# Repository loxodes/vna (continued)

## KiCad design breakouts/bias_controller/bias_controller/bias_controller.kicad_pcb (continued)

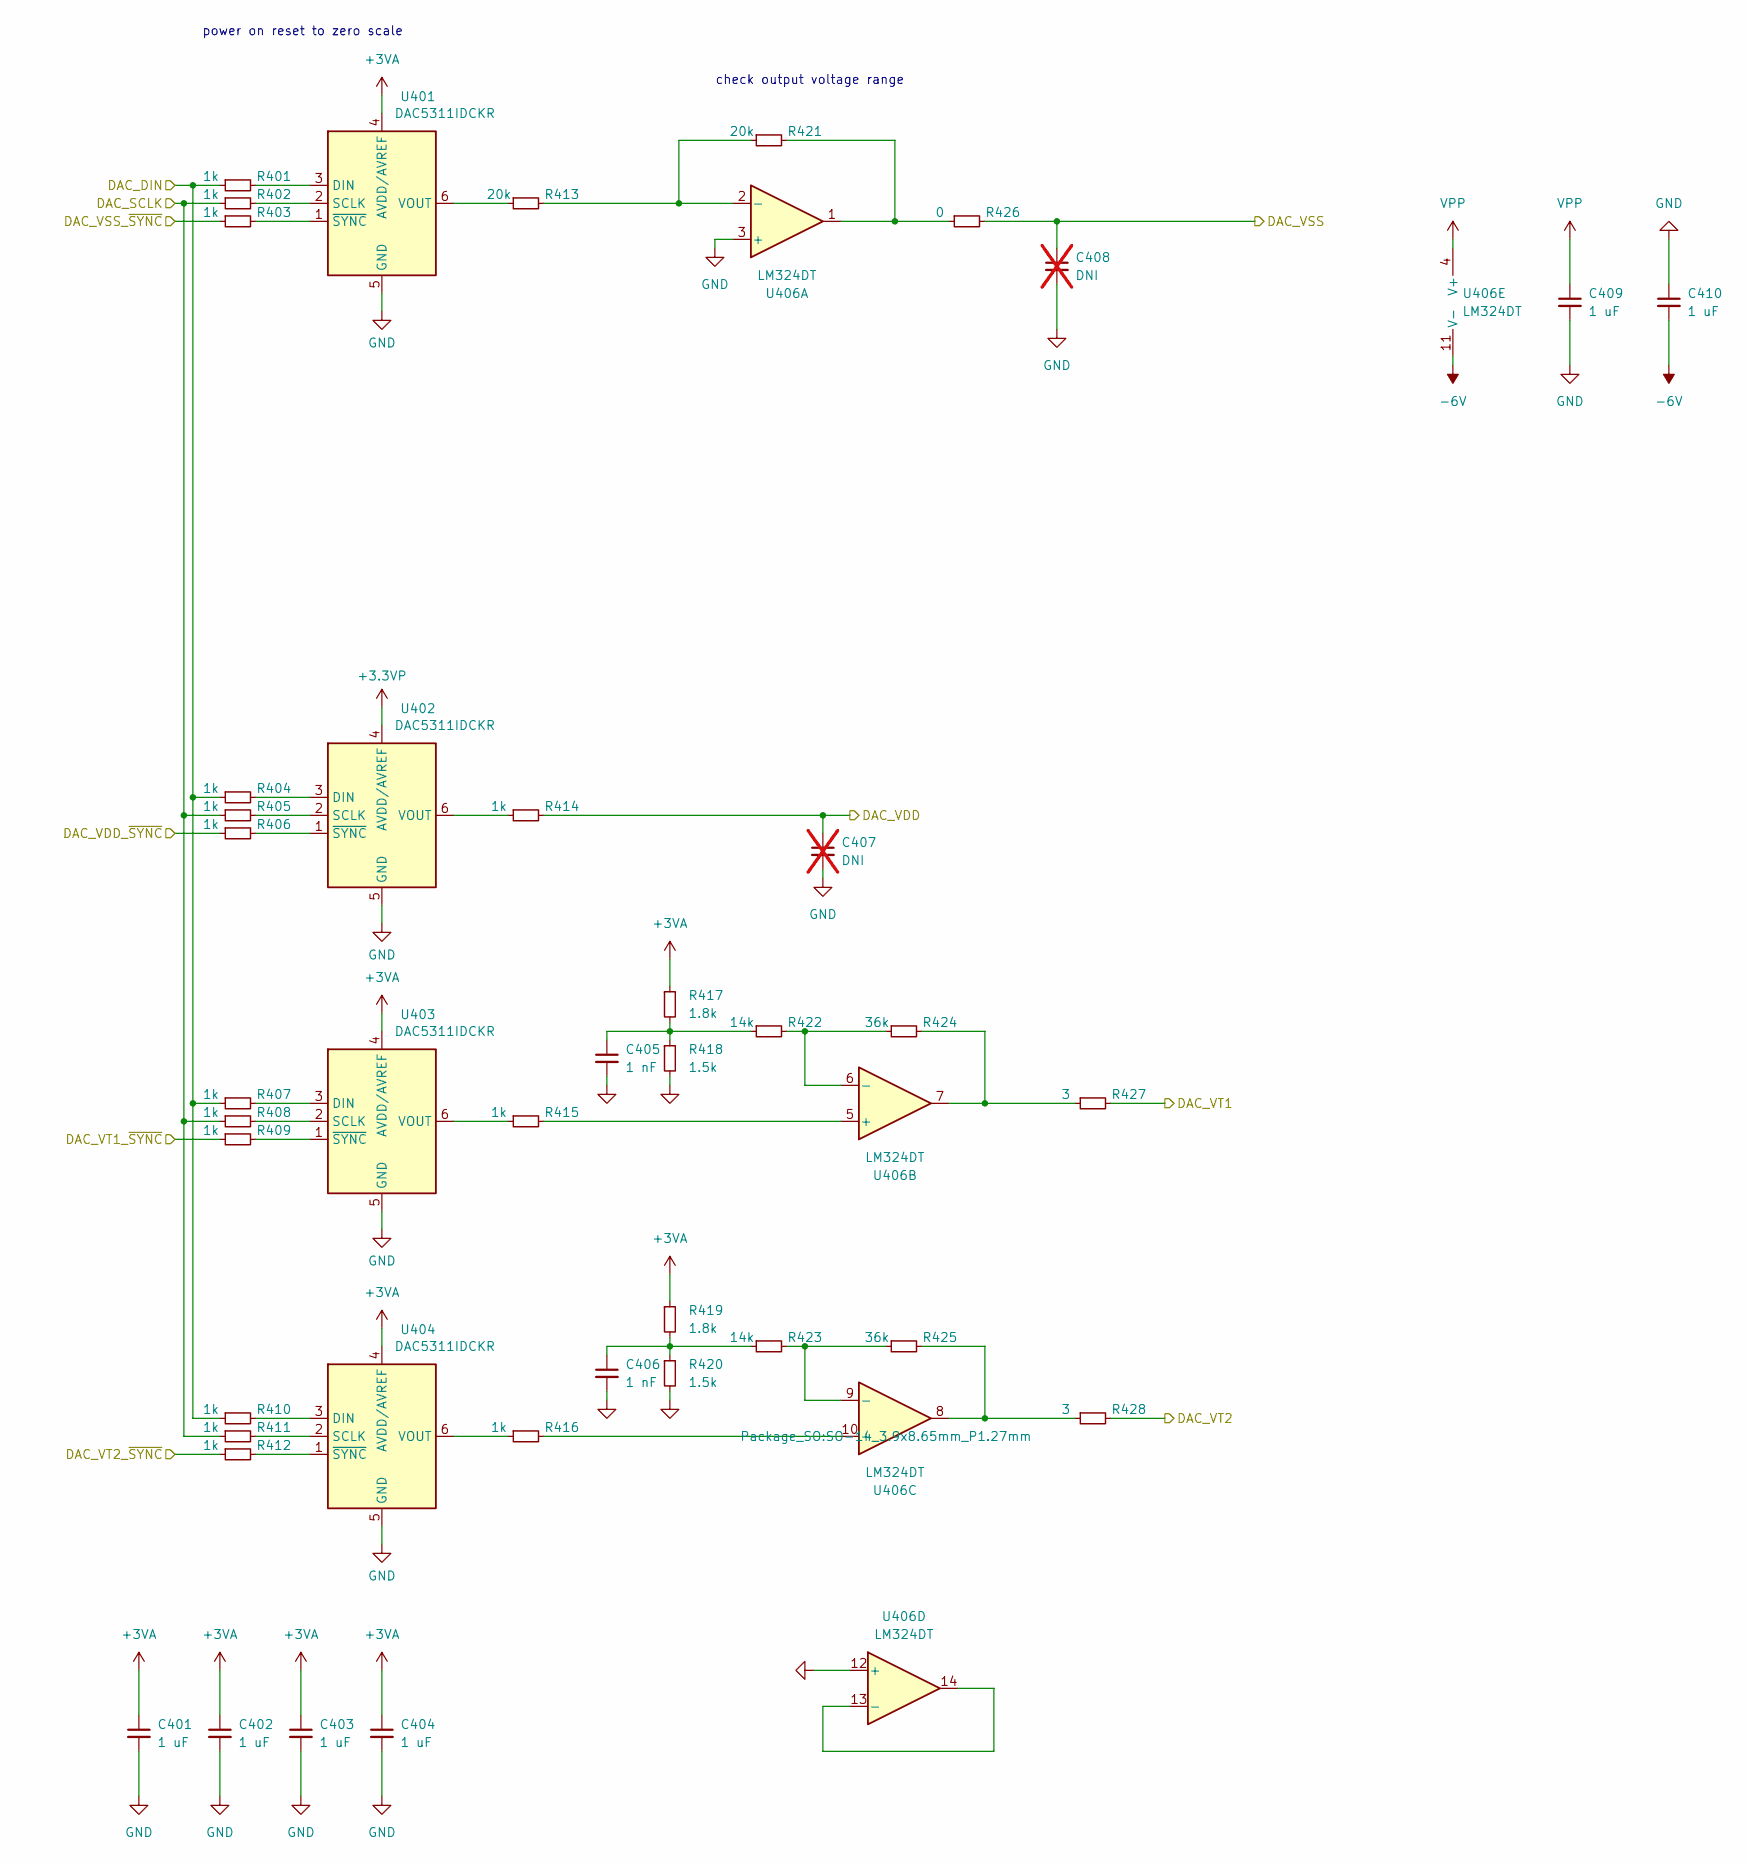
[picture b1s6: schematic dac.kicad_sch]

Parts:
C401, C402, C403, C404, C409, C410: 1 uF; C_0402_1005Metric
C405, C406: 1 nF; C_0402_1005Metric
C407, C408: DNI; C_0402_1005Metric; not fitted
R401, R402, R403, R404, R405, R406, R407, R408, R409, R410, R411, R412, R414, R415, R416: 1k; R_0402_1005Metric
R413, R421: 20k; R_0402_1005Metric
R417, R419: 1.8k; R_0402_1005Metric
R418, R420: 1.5k; R_0402_1005Metric
R422, R423: 14k; R_0402_1005Metric
R424, R425: 36k; R_0402_1005Metric
R426: 0; R_0402_1005Metric
R427, R428: 3; R_0402_1005Metric
U401, U402, U403, U404: DAC5311IDCKR; SOT-363_SC-70-6
U406: LM324DT; SO-14_3.9x8.65mm_P1.27mm

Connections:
+3.3VP: U402.4 (AVDD/AVREF); also elsewhere on the board
+3VA: C401.1, C402.1, C403.1, C404.1, R417.1, R419.1, U401.4 (AVDD/AVREF), U403.4 (AVDD/AVREF), U404.4 (AVDD/AVREF); also elsewhere on the board
-6V: C410.2, U406.11 (V-); also elsewhere on the board
/dac/DAC_DIN: R401.1, R404.1, R407.1, R410.1; also elsewhere on the board
/dac/DAC_SCLK: R402.1, R405.1, R408.1, R411.1; also elsewhere on the board
/dac/DAC_VDD: C407.1, R414.2; also elsewhere on the board
/dac/DAC_VDD_~SYNC: R406.1; also elsewhere on the board
/dac/DAC_VSS: C408.1, R426.2; also elsewhere on the board
/dac/DAC_VSS_~SYNC: R403.1; also elsewhere on the board
/dac/DAC_VT1: R427.2; also elsewhere on the board
/dac/DAC_VT1_~SYNC: R409.1; also elsewhere on the board
/dac/DAC_VT2: R428.2; also elsewhere on the board
/dac/DAC_VT2_~SYNC: R412.1; also elsewhere on the board
GND: C401.2, C402.2, C403.2, C404.2, C405.2, C406.2, C407.2, C408.2, C409.2, C410.1, R418.2, R420.2, U401.5 (GND), U402.5 (GND), U403.5 (GND), U404.5 (GND), U406.3 (+), U406.12 (+); also elsewhere on the board
unnamed: C405.1, R417.2, R418.1, R422.1
unnamed: C406.1, R419.2, R420.1, R423.1
unnamed: R421.2, R426.1, U406.1
unnamed: R424.2, R427.1, U406.7
unnamed: R425.2, R428.1, U406.8
unnamed: R401.2, U401.3 (DIN)
unnamed: R402.2, U401.2 (SCLK)
unnamed: R413.1, U401.6 (VOUT)
unnamed: R403.2, U401.1 (~SYNC)
unnamed: R404.2, U402.3 (DIN)
unnamed: R405.2, U402.2 (SCLK)
unnamed: R414.1, U402.6 (VOUT)
unnamed: R406.2, U402.1 (~SYNC)
unnamed: R407.2, U403.3 (DIN)
unnamed: R408.2, U403.2 (SCLK)
unnamed: R415.1, U403.6 (VOUT)
unnamed: R409.2, U403.1 (~SYNC)
unnamed: R410.2, U404.3 (DIN)
unnamed: R411.2, U404.2 (SCLK)
unnamed: R416.1, U404.6 (VOUT)
unnamed: R412.2, U404.1 (~SYNC)
unnamed: R413.2, R421.1, U406.2 (-)
unnamed: R415.2, U406.5 (+)
unnamed: R422.2, R424.1, U406.6 (-)
unnamed: R416.2, U406.10 (+)
unnamed: R423.2, R425.1, U406.9 (-)
unnamed: U406.13 (-), U406.14
VPP: C409.1, U406.4 (V+); also elsewhere on the board

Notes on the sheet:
check output voltage range
power on reset to zero scale

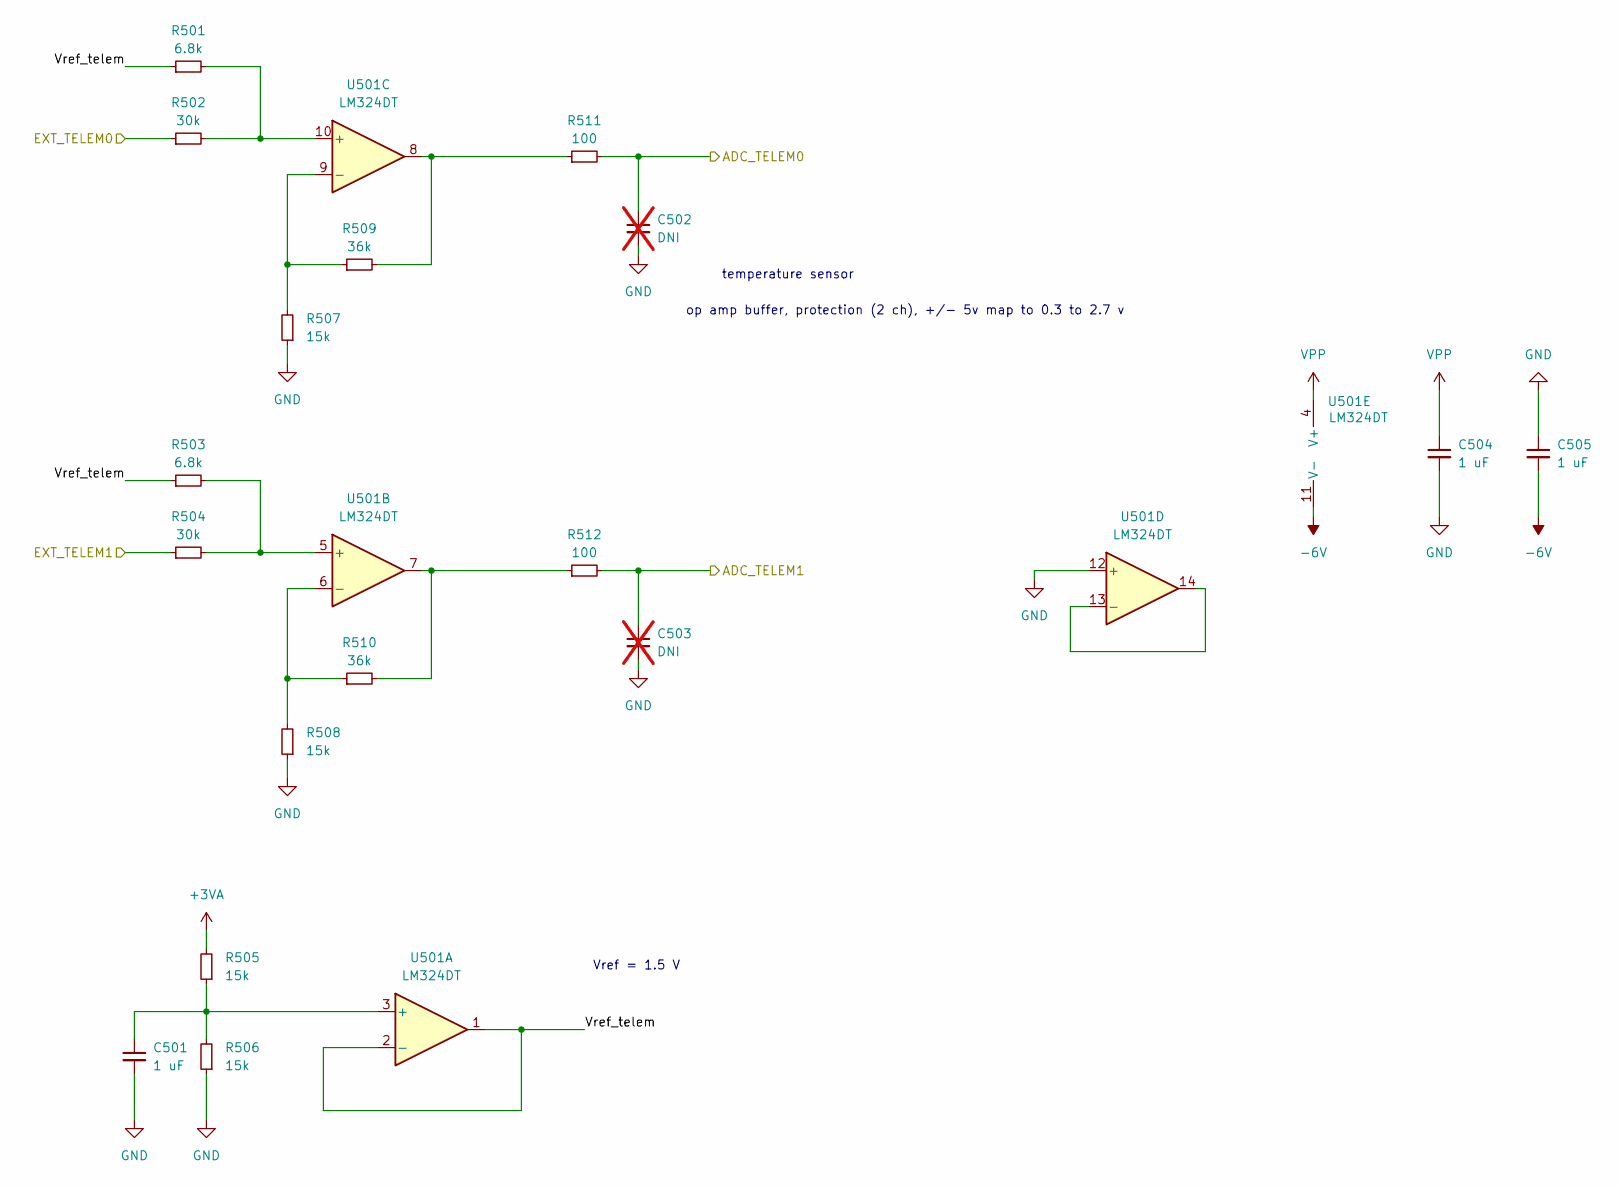
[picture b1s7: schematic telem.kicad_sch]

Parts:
C501, C504, C505: 1 uF; C_0402_1005Metric
C502, C503: DNI; C_0402_1005Metric; not fitted
R501, R503: 6.8k; R_0402_1005Metric
R502, R504: 30k; R_0402_1005Metric
R505, R506, R507, R508: 15k; R_0402_1005Metric
R509, R510: 36k; R_0402_1005Metric
R511, R512: 100; R_0402_1005Metric
U501: LM324DT; SO-14_3.9x8.65mm_P1.27mm

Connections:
+3VA: R505.2; also elsewhere on the board
-6V: C505.2, U501.11 (V-); also elsewhere on the board
/ext_conn/EXT_TELEM0: R502.1; also elsewhere on the board
/ext_conn/EXT_TELEM1: R504.1; also elsewhere on the board
/mcu/ADC_TELEM0: C502.1, R511.2; also elsewhere on the board
/mcu/ADC_TELEM1: C503.1, R512.2; also elsewhere on the board
/telemetry/Vref_telem: R501.1, R503.1, U501.1, U501.2 (-)
GND: C501.2, C502.2, C503.2, C504.2, C505.1, R506.1, R507.1, R508.1, U501.12 (+); also elsewhere on the board
unnamed: R509.2, R511.1, U501.8
unnamed: R510.2, R512.1, U501.7
unnamed: C501.1, R505.1, R506.2, U501.3 (+)
unnamed: R503.2, R504.2, U501.5 (+)
unnamed: R508.2, R510.1, U501.6 (-)
unnamed: R501.2, R502.2, U501.10 (+)
unnamed: R507.2, R509.1, U501.9 (-)
unnamed: U501.13 (-), U501.14
VPP: C504.1, U501.4 (V+); also elsewhere on the board

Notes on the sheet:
op amp buffer, protection (2 ch), +/- 5v map to 0.3 to 2.7 v
temperature sensor
Vref = 1.5 V

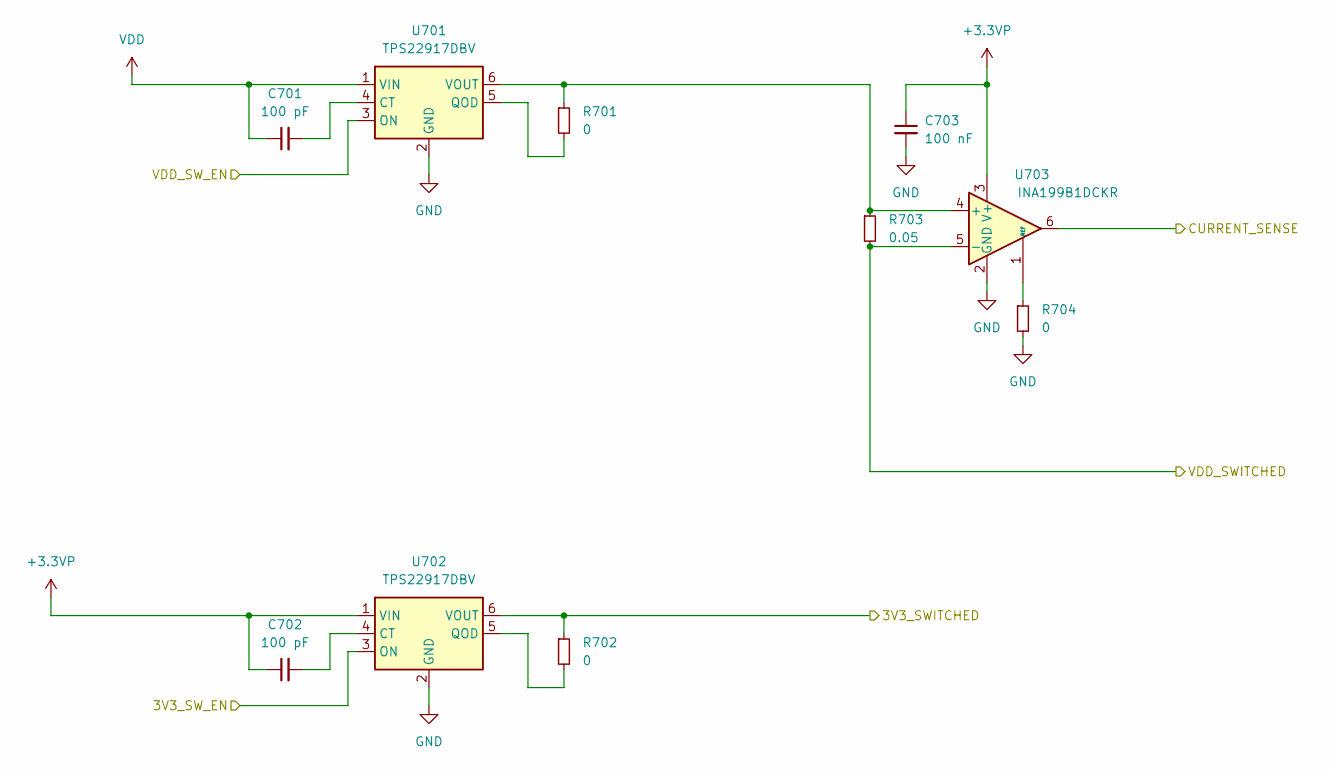
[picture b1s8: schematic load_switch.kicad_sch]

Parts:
C701, C702: 100 pF; C_0402_1005Metric
C703: 100 nF; C_0402_1005Metric
R701, R702: 0; R_0402_1005Metric
R703: 0.05; R_1206_3216Metric
R704: 0; R_1206_3216Metric
U701, U702: TPS22917DBV; SOT-23-6
U703: INA199B1DCKR; SOT-363_SC-70-6

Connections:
+3.3VP: C702.1, C703.1, U702.1 (VIN), U703.3 (V+); also elsewhere on the board
/ext_conn/3V3_SWITCHED: R702.1, U702.6 (VOUT); also elsewhere on the board
/ext_conn/VDD_SWITCHED: R703.2, U703.5 (-); also elsewhere on the board
/load switch/CURRENT_SENSE: U703.6; also elsewhere on the board
/mcu/3V3_SW_EN: U702.3 (ON); also elsewhere on the board
/mcu/VDD_SW_EN: U701.3 (ON); also elsewhere on the board
GND: C703.2, R704.2, U701.2 (GND), U702.2 (GND), U703.2 (GND); also elsewhere on the board
unnamed: C701.2, U701.4 (CT)
unnamed: R701.2, U701.5 (QOD)
unnamed: R701.1, R703.1, U701.6 (VOUT), U703.4 (+)
unnamed: C702.2, U702.4 (CT)
unnamed: R702.2, U702.5 (QOD)
unnamed: R704.1, U703.1 (REF)
VDD: C701.1, U701.1 (VIN); also elsewhere on the board

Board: 2 copper layers, 203 parts (0 on the bottom side), 164 nets, no tracks yet.

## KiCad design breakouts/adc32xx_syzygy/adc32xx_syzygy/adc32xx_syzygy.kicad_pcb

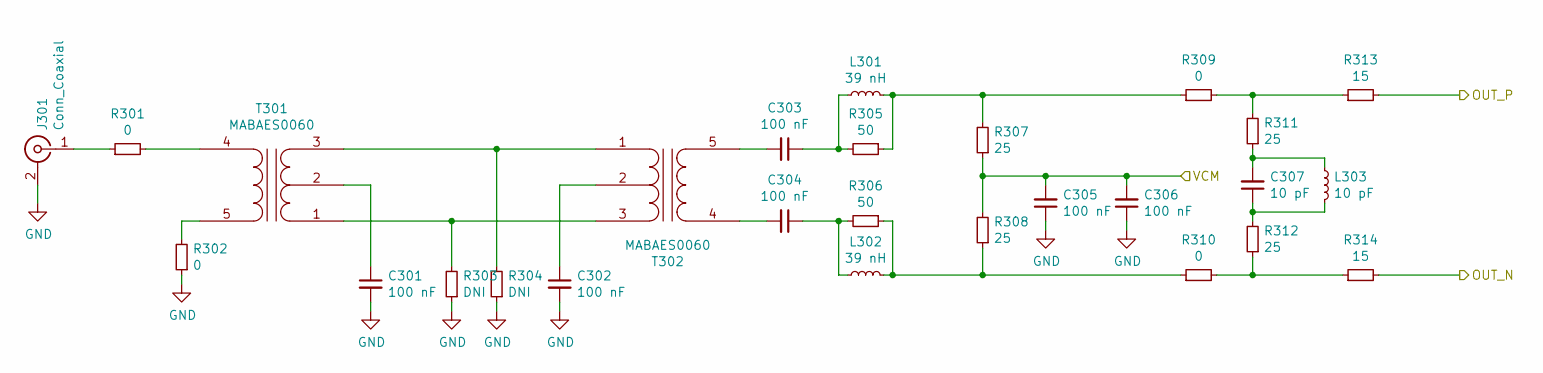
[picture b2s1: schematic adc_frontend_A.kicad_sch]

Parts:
C301, C302, C303, C304, C305, C306: 100 nF; C_0402_1005Metric
C307: 10 pF; C_0402_1005Metric
J301: Conn_Coaxial; SMA_Cinch_142-0711-821_EdgeMount
L301, L302: 39 nH; R_0402_1005Metric
L303: 10 pF; R_0402_1005Metric
R301, R302, R309, R310: 0; R_0402_1005Metric
R303, R304: DNI; R_0402_1005Metric
R305, R306: 50; R_0402_1005Metric
R307, R308, R311, R312: 25; R_0402_1005Metric
R313, R314: 15; R_0402_1005Metric
T301, T302: MABAES0060; 5LEAD_BALUN_4p83mm_3p3mm

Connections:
/VCM: C305.2, C306.2, R307.1, R308.2; also elsewhere on the board
/adc/IN_A_N: R314.2; also elsewhere on the board
/adc/IN_A_P: R313.2; also elsewhere on the board
GND: C301.2, C302.2, C305.1, C306.1, J301.2 (Ext), R302.1, R303.1, R304.1; also elsewhere on the board
unnamed: C303.1, L301.1, R305.2
unnamed: C304.1, L302.1, R306.2
unnamed: C307.1, L303.2, R312.2
unnamed: C307.2, L303.1, R311.1
unnamed: J301.1 (In), R301.1
unnamed: L301.2, R305.1, R307.2, R309.1
unnamed: L302.2, R306.1, R308.1, R310.1
unnamed: R309.2, R311.2, R313.1
unnamed: R310.2, R312.1, R314.1
unnamed: C301.1, T301.2 (PM)
unnamed: R303.2, T301.1 (PR1), T302.3 (PR2)
unnamed: R304.2, T301.3 (PR2), T302.1 (PR1)
unnamed: R301.2, T301.4 (S1)
unnamed: R302.2, T301.5 (S2)
unnamed: C302.1, T302.2 (PM)
unnamed: C304.2, T302.4 (S1)
unnamed: C303.2, T302.5 (S2)

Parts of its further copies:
C401, C402, C403, C404, C405, C406: 100 nF; C_0402_1005Metric
C407: 10 pF; C_0402_1005Metric
J401: Conn_Coaxial; SMA_Cinch_142-0711-821_EdgeMount
L401, L402: 39 nH; R_0402_1005Metric
L403: 10 pF; R_0402_1005Metric
R401, R402, R409, R410: 0; R_0402_1005Metric
R403, R404: DNI; R_0402_1005Metric
R405, R406: 50; R_0402_1005Metric
R407, R408, R411, R412: 25; R_0402_1005Metric
R413, R414: 15; R_0402_1005Metric
T401, T402: MABAES0060; 5LEAD_BALUN_4p83mm_3p3mm

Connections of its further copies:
/VCM: C405.2, C406.2, R407.1, R408.2; also elsewhere on the board
/adc/IN_B_N: R414.2; also elsewhere on the board
/adc/IN_B_P: R413.2; also elsewhere on the board
GND: C401.2, C402.2, C405.1, C406.1, J401.2 (Ext), R402.1, R403.1, R404.1; also elsewhere on the board
unnamed: C403.1, L401.1, R405.2
unnamed: C404.1, L402.1, R406.2
unnamed: C407.1, L403.2, R412.2
unnamed: C407.2, L403.1, R411.1
unnamed: J401.1 (In), R401.1
unnamed: L401.2, R405.1, R407.2, R409.1
unnamed: L402.2, R406.1, R408.1, R410.1
unnamed: R409.2, R411.2, R413.1
unnamed: R410.2, R412.1, R414.1
unnamed: C401.1, T401.2 (PM)
unnamed: R403.2, T401.1 (PR1), T402.3 (PR2)
unnamed: R404.2, T401.3 (PR2), T402.1 (PR1)
unnamed: R401.2, T401.4 (S1)
unnamed: R402.2, T401.5 (S2)
unnamed: C402.1, T402.2 (PM)
unnamed: C404.2, T402.4 (S1)
unnamed: C403.2, T402.5 (S2)

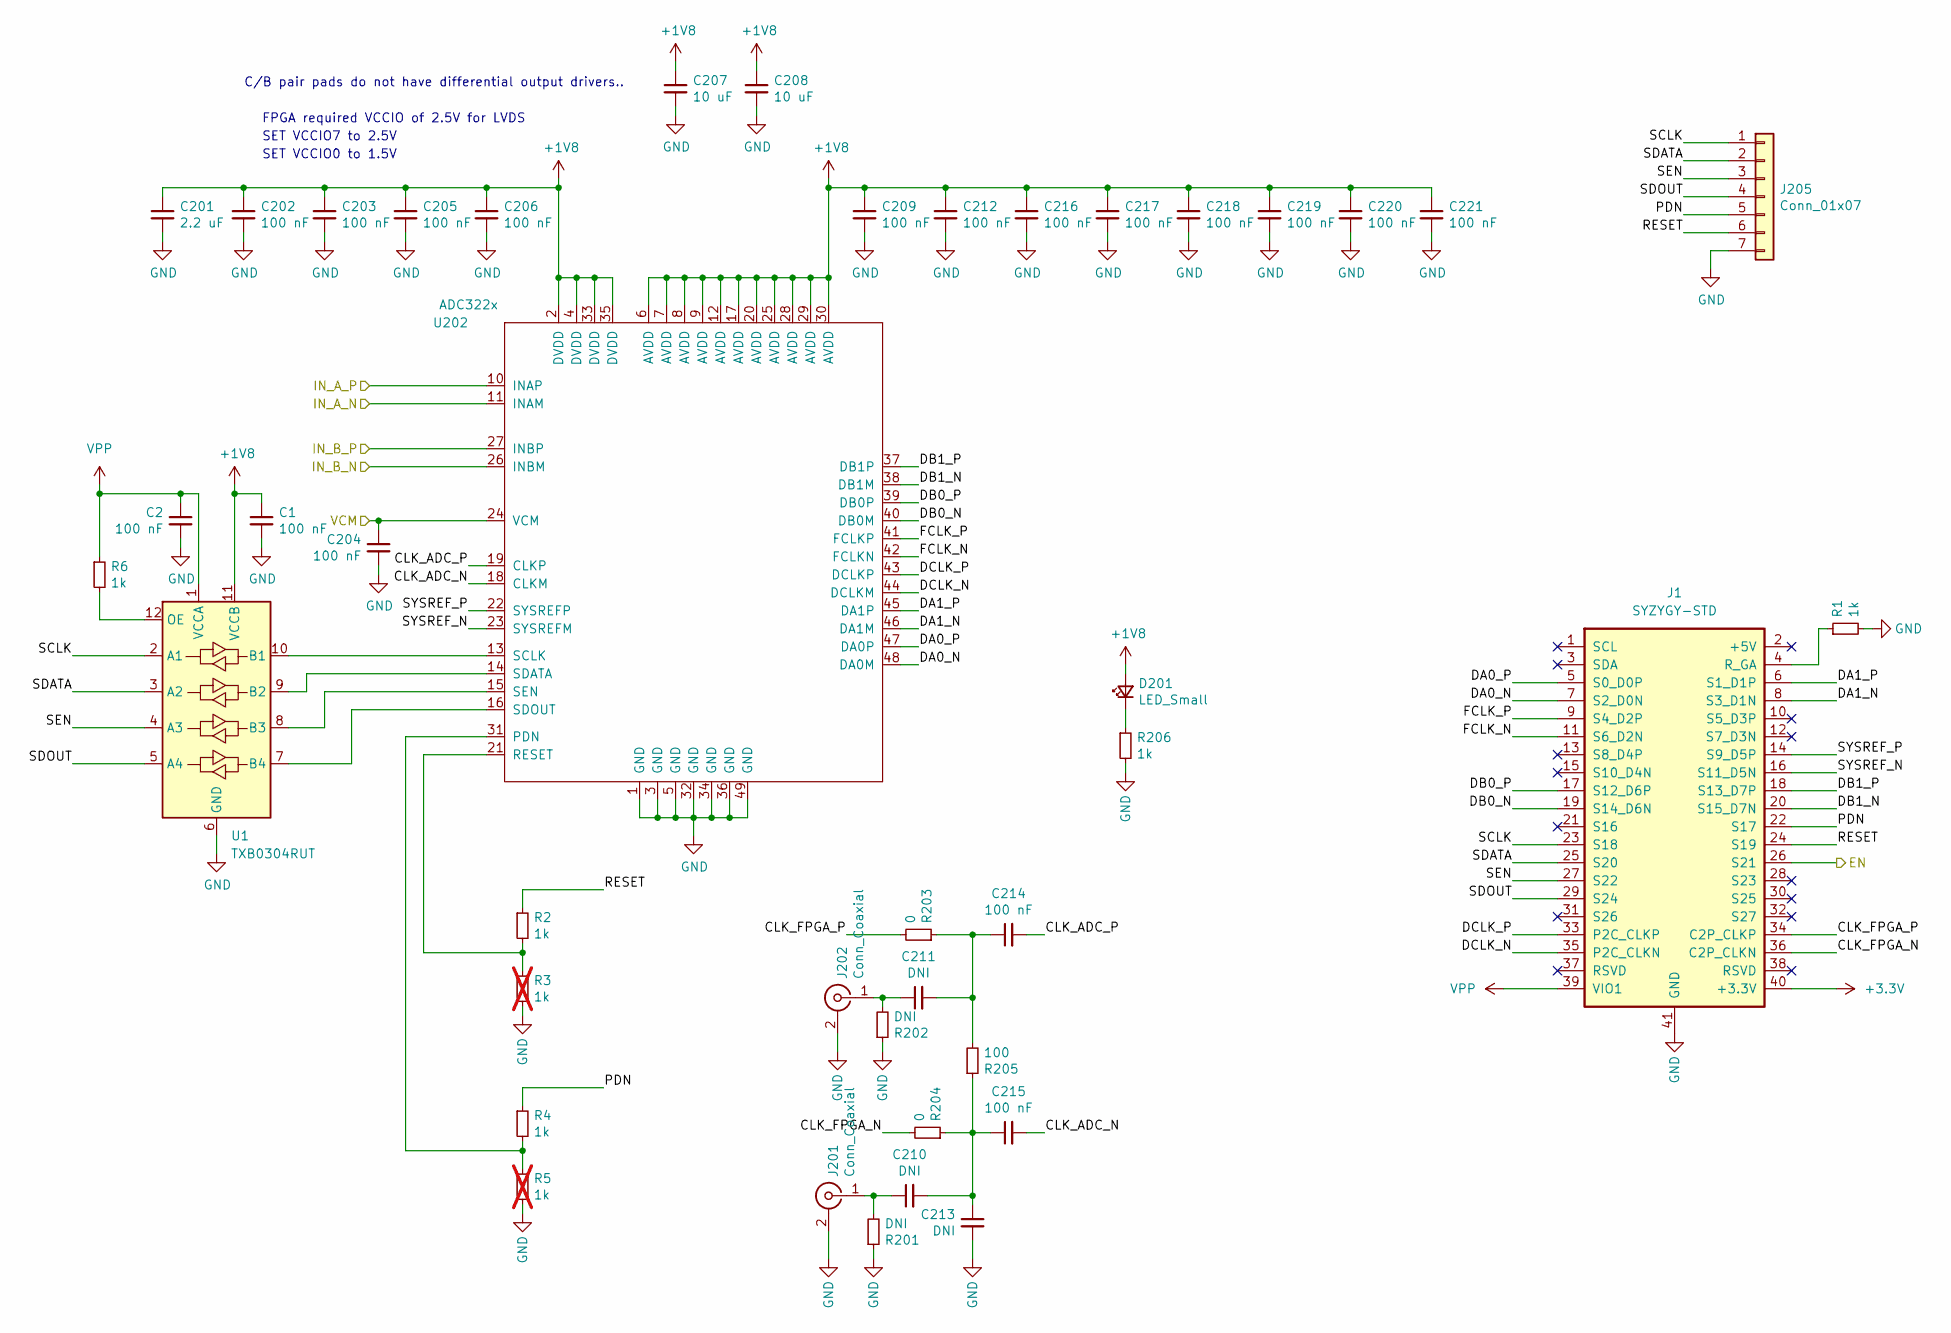
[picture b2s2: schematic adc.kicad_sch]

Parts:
C1, C2, C202, C203, C204, C205, C206, C209, C212, C214, C215, C216, C217, C218, C219, C220, C221: 100 nF; C_0402_1005Metric
C201: 2.2 uF; C_0603_1608Metric
C207, C208: 10 uF; C_0603_1608Metric
C210, C211, C213: DNI; C_0402_1005Metric
D201: LED_Small; LED_0603_1608Metric
J1: SYZYGY-STD; SYZYGY_standard_pod
J201, J202: Conn_Coaxial; U.FL_Hirose_U.FL-R-SMT-1_Vertical
J205: Conn_01x07; PinSocket_1x07_P2.54mm_Vertical
R1, R2, R4, R6, R206: 1k; R_0402_1005Metric
R3, R5: 1k; R_0402_1005Metric; not fitted
R201, R202: DNI; R_0402_1005Metric
R203, R204: 0; R_0402_1005Metric
R205: 100; R_0402_1005Metric
U1: TXB0304RUT; Texas_R-PUQFN-N12
U202: ADC322x; QFN-48-1EP_7x7mm_P0.5mm_EP5.6x5.6mm

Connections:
+1V8: C1.1, C201.1, C202.1, C203.1, C205.1, C206.1, C207.1, C208.1, C209.1, C212.1, C216.1, C217.1, C218.1, C219.1, C220.1, C221.1, D201.2 (A), U1.11 (VCCB), U202.2 (DVDD), U202.4 (DVDD), U202.6 (AVDD), U202.7 (AVDD), U202.8 (AVDD), U202.9 (AVDD), U202.12 (AVDD), U202.17 (AVDD), U202.20 (AVDD), U202.25 (AVDD), U202.28 (AVDD), U202.29 (AVDD), U202.30 (AVDD), U202.33 (DVDD), U202.35 (DVDD); also elsewhere on the board
+3.3V: J1.40 (+3.3V); also elsewhere on the board
/VCM: C204.1, U202.24 (VCM); also elsewhere on the board
/adc/CLK_ADC_N: C215.2, U202.18 (CLKM)
/adc/CLK_ADC_P: C214.2, U202.19 (CLKP)
/adc/CLK_FPGA_N: J1.36 (C2P_CLKN), R204.2
/adc/CLK_FPGA_P: J1.34 (C2P_CLKP), R203.2
/adc/DA0_N: J1.7 (S2_D0N), U202.48 (DA0M)
/adc/DA0_P: J1.5 (S0_D0P), U202.47 (DA0P)
/adc/DA1_N: J1.8 (S3_D1N), U202.46 (DA1M)
/adc/DA1_P: J1.6 (S1_D1P), U202.45 (DA1P)
/adc/DB0_N: J1.19 (S14_D6N), U202.40 (DB0M)
/adc/DB0_P: J1.17 (S12_D6P), U202.39 (DB0P)
/adc/DB1_N: J1.20 (S15_D7N), U202.38 (DB1M)
/adc/DB1_P: J1.18 (S13_D7P), U202.37 (DB1P)
/adc/DCLK_N: J1.35 (P2C_CLKN), U202.44 (DCLKM)
/adc/DCLK_P: J1.33 (P2C_CLKP), U202.43 (DCLKP)
/adc/EN: J1.26 (S21); also elsewhere on the board
/adc/FCLK_N: J1.11 (S6_D2N), U202.42 (FCLKN)
/adc/FCLK_P: J1.9 (S4_D2P), U202.41 (FCLKP)
/adc/IN_A_N: U202.11 (INAM); also elsewhere on the board
/adc/IN_A_P: U202.10 (INAP); also elsewhere on the board
/adc/IN_B_N: U202.26 (INBM); also elsewhere on the board
/adc/IN_B_P: U202.27 (INBP); also elsewhere on the board
/adc/PDN: J1.22 (S17), J205.5, R4.1
/adc/RESET: J1.24 (S19), J205.6, R2.1
/adc/SCLK: J1.23 (S18), J205.1, U1.2 (A1)
/adc/SDATA: J1.25 (S20), J205.2, U1.3 (A2)
/adc/SDOUT: J1.29 (S24), J205.4, U1.5 (A4)
/adc/SEN: J1.27 (S22), J205.3, U1.4 (A3)
/adc/SYSREF_N: J1.16 (S11_D5N), U202.23 (SYSREFM)
/adc/SYSREF_P: J1.14 (S9_D5P), U202.22 (SYSREFP)
GND: C1.2, C2.2, C201.2, C202.2, C203.2, C204.2, C205.2, C206.2, C207.2, C208.2, C209.2, C212.2, C213.2, C216.2, C217.2, C218.2, C219.2, C220.2, C221.2, J1.41 (GND), J201.2 (Ext), J202.2 (Ext), J205.7, R1.2, R3.2, R5.2, R201.1, R202.1, R206.2, U1.6 (GND), U202.1 (GND), U202.3 (GND), U202.5 (GND), U202.32 (GND), U202.34 (GND), U202.36 (GND), U202.49 (GND); also elsewhere on the board
unnamed: C210.2, C213.1, C215.1, R204.1, R205.1
unnamed: C211.2, C214.1, R203.1, R205.2
unnamed: D201.1 (K), R206.1
unnamed: J1.4 (R_GA), R1.1
unnamed: C210.1, J201.1 (In), R201.2
unnamed: C211.1, J202.1 (In), R202.2
unnamed: U1.10 (B1), U202.13 (SCLK)
unnamed: U1.9 (B2), U202.14 (SDATA)
unnamed: U1.8 (B3), U202.15 (SEN)
unnamed: U1.7 (B4), U202.16 (SDOUT)
unnamed: R6.2, U1.12 (OE)
unnamed: R4.2, R5.1, U202.31 (PDN)
unnamed: R2.2, R3.1, U202.21 (RESET)
VPP: C2.1, J1.39 (VIO1), R6.1, U1.1 (VCCA)

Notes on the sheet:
SET VCCIO0 to 1.5V
SET VCCIO7 to 2.5V
FPGA required VCCIO of 2.5V for LVDS
C/B pair pads do not have differential output drivers..

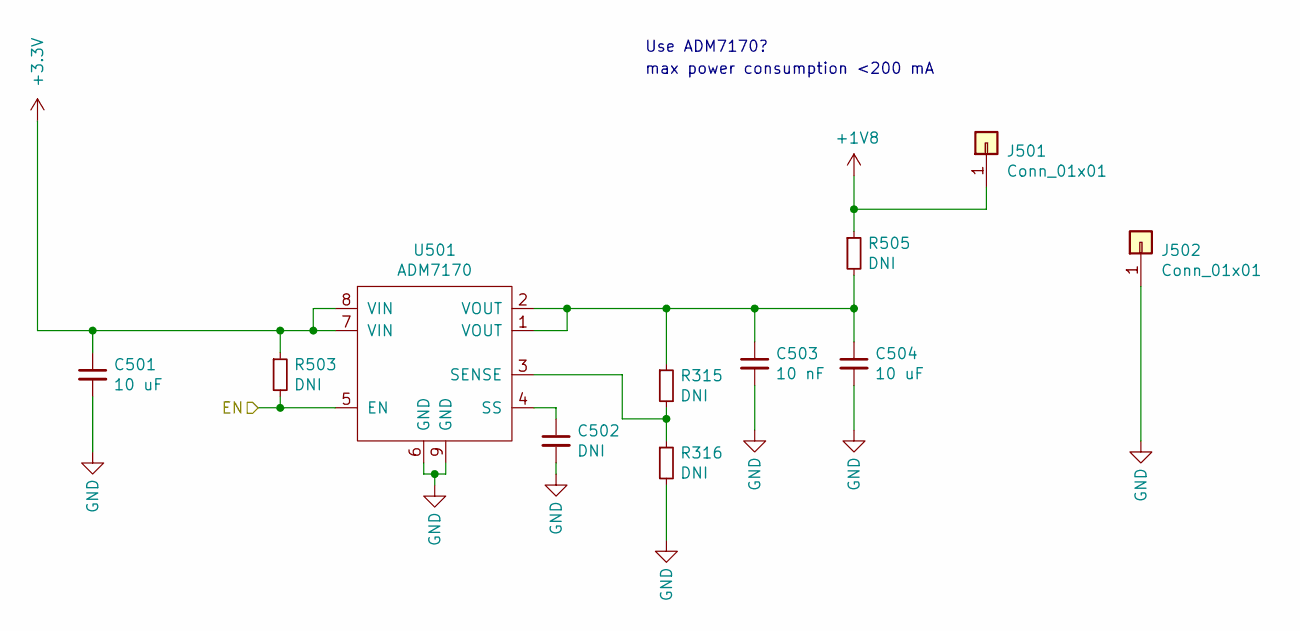
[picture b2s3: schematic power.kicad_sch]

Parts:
C501, C504: 10 uF; C_0603_1608Metric
C502: DNI; C_0402_1005Metric
C503: 10 nF; C_0402_1005Metric
J501, J502: Conn_01x01; TestPoint_Keystone_5015_Micro-Minature
R315, R316, R503, R505: DNI; R_0402_1005Metric
U501: ADM7170; DFN-8-1EP_3x3mm_P0.5mm_EP1.66x2.38mm

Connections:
+1V8: J501.1, R505.1; also elsewhere on the board
+3.3V: C501.1, R503.1, U501.7 (VIN), U501.8 (VIN); also elsewhere on the board
/adc/EN: R503.2, U501.5 (EN); also elsewhere on the board
GND: C501.2, C502.2, C503.2, C504.2, J502.1, R316.2, U501.6 (GND), U501.9 (GND); also elsewhere on the board
unnamed: C503.1, C504.1, R315.1, R505.2, U501.1 (VOUT), U501.2 (VOUT)
unnamed: R315.2, R316.1, U501.3 (SENSE)
unnamed: C502.1, U501.4 (SS)

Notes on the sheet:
max power consumption <200 mA
Use ADM7170?

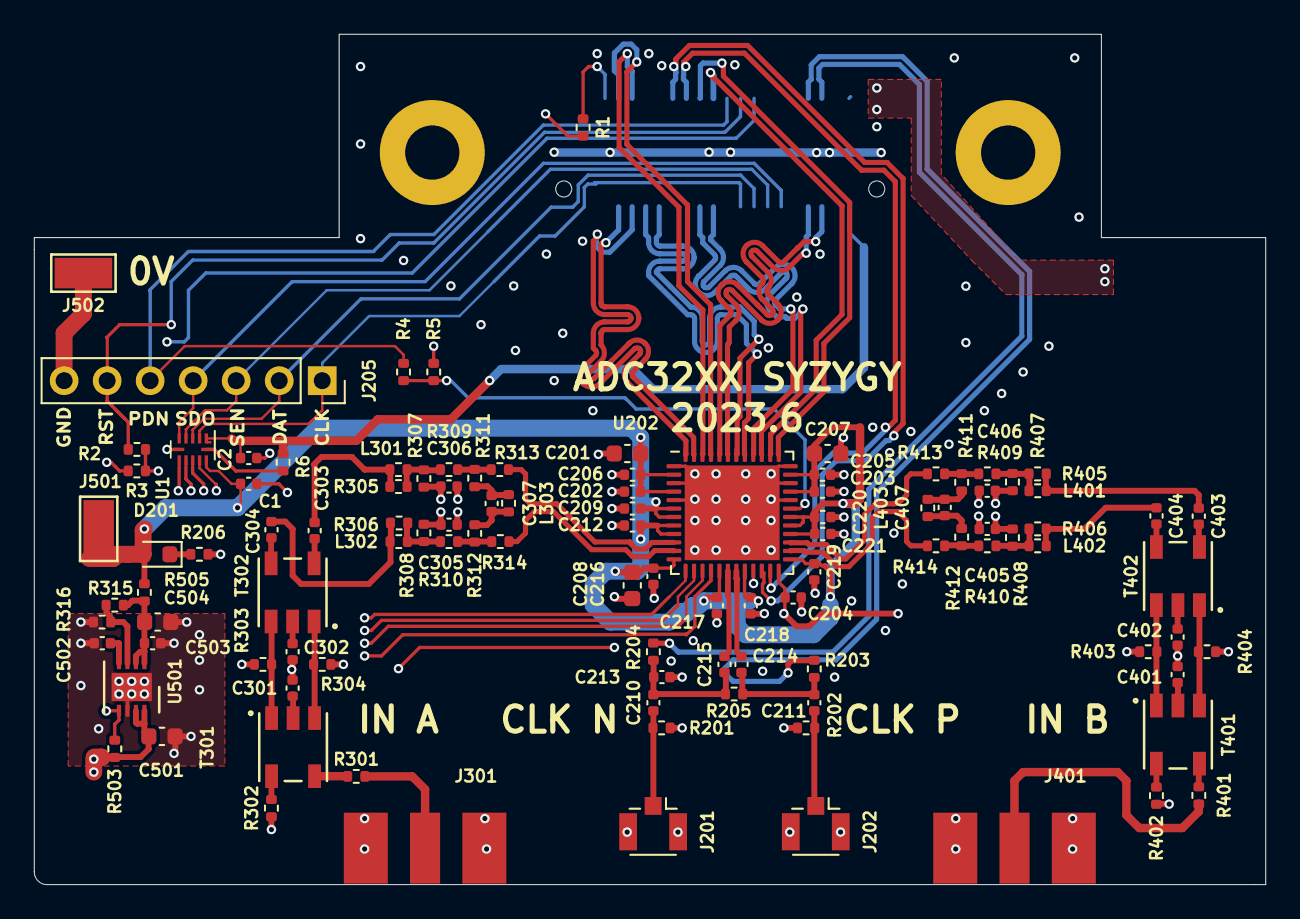
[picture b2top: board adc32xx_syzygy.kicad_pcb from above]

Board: 4 copper layers, 72.7 x 50.2 mm, 107 parts (1 on the bottom side), 84 nets.

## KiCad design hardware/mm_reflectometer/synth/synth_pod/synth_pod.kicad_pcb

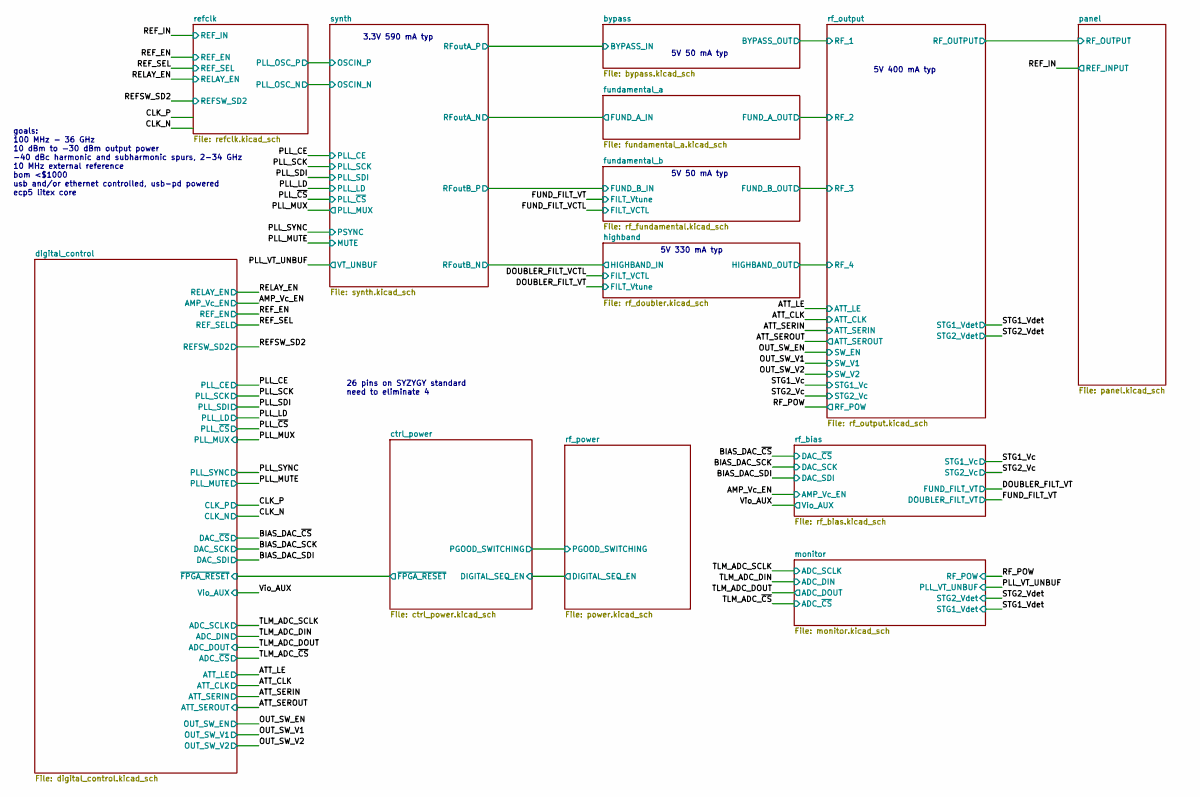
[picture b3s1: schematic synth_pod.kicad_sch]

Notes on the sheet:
5V 330 mA typ
5V 50 mA typ
5V 400 mA typ
3.3V 590 mA typ
goals: 100 MHz - 36 GHz 10 dBm to -30 dBm output power -40 dBc harmonic and subharmonic spurs, 2-34 GHz 10 MHz external reference bom <$1000 usb and/or ethernet controlled, usb-pd powered ecp5 litex core
26 pins on SYZYGY standard need to eliminate 4
